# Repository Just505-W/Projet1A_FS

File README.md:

# Projet1A\_FS

Bienvenu sur le dépot GitHub d'un des groupes de Projet de première année de l'ENSEA.   
Participants du projet :   
BALLARD Athénaïs           NOICI Amélie  
EL GAAMOUCH Aïssa      VENTURA Arthur  
ELICE Bastien                    WOELFFEL Justine  
GERVAIS Joseph

Professeur encadrant : M.TAUVEL

## Dossiers utiles :

Projet Datalogger/SD d'un etudiant sur Git : https://github.com/crsz20/SDCard-Interface-STM32/tree/master

Régulateur de tension datasheet : https://www.alldatasheet.com/datasheet-pdf/view/807123/TI1/LM1117DT-3.3.html

Comment éditer un fichier GitHub : https://docs.github.com/fr/get-started/writing-on-github/getting-started-with-writing-and-formatting-on-github/basic-writing-and-formatting-syntax

Tutoriel de conception de PCB : https://jak-services.github.io/fr/tutorial\_kicad\_9\_build\_your\_first\_pcb.html

:warning: ***Remplir le fichier Suivi de projet.md à la fin de chaque séance !***

## Description du projet:

Ce projet a pour objectif de réaliser des composants utiles au bon fonctionnement d'une monoplace dans le cadre du concours **FORMULA STUDENT**. Un de ces composants est lui tiré du concours **PERSEUS**.

Le projet se concentre sur la conception et la fabrication de 3 PCB:

* Un capteur d'**Odométrie** : il calcule la vitesse de rotation des roues de la voitures et la transmet au bus CAN.
* Un capteur **BMS** (battery management system) : un système électronique permettant d’indiquer au conducteur la charge de la batterie en temps réel.

* Un **Datalogger**:  il récupère les données du bus CAN en temps réel et les stock dans un carte SD, qui servira de "boîte noire" en cas de destruction de l'appareil. Il sera également doté d'une application codée en Java (référence à notre super cours de **programmation orientée objet**) afin d'avoir une interface graphique utile à la conduite.

## Rôles

|Chef de projet|Odométrie|Datalogger|BMS|Software|
|:-:|:-:|:-:|:-:|:-:|
|Justine|Athénaïs|Aïssa \\ Joseph|Arthur|Amélie \\ Bastien|

## Odométrie Spécifications :

### Composants nécessaires + Datasheet :

* Microcontrôleur: STM32C092FCP6 (code : 4676916 - Farnell)
* Régulateur de tension : (code : 197-7195P - RS)
* Connecteur USB :
* 4 connecteurs d'entrée/sortie :
* 2 boutons poussoir : \~Interrupteur tactile traversant (code : 682-1254 - RS)\~
* 2 LED (LED de fonctionnement et de test) : (code : 466-3863 - RS)

## Datalogger Spécifications :

### Composants nécessaires + Datasheet :

* Microcontrôleur : STM32F042F6P6 (code : 2469549 - Farnell)
* 2 Régulateur de tension : Regulateur 3.3V (code : 197-7195P - RS) Régulateur 5.0V (code : 2534281 - Farnell)
* 4 connecteurs d'entrée/sortie :
* 1 Interrupteur : Interrupteur tactile traversant (code : 682-1254 - RS)
* 2 boutons poussoir :
* 2 LED (LED de fonctionnement et de test) : LED CMS  (code : 466-3863 - RS)

## Gestionnaire de Batterie (BMS) :

### Composants nécessaires + Datasheet :

* Microcontrôleur: STM32C092FCP6 (code : 4676916 - Farnell)
* Régulateur de tension : (code : 197-7195P - RS)
* 4 connecteurs d'entrée/sortie :
* 2 boutons poussoir : \~Interrupteur tactile traversant (code : 682-1254 - RS)\~
* 2 LED (LED de fonctionnement et de test) : (code : 466-3863 - RS)
* capteur à effet hall

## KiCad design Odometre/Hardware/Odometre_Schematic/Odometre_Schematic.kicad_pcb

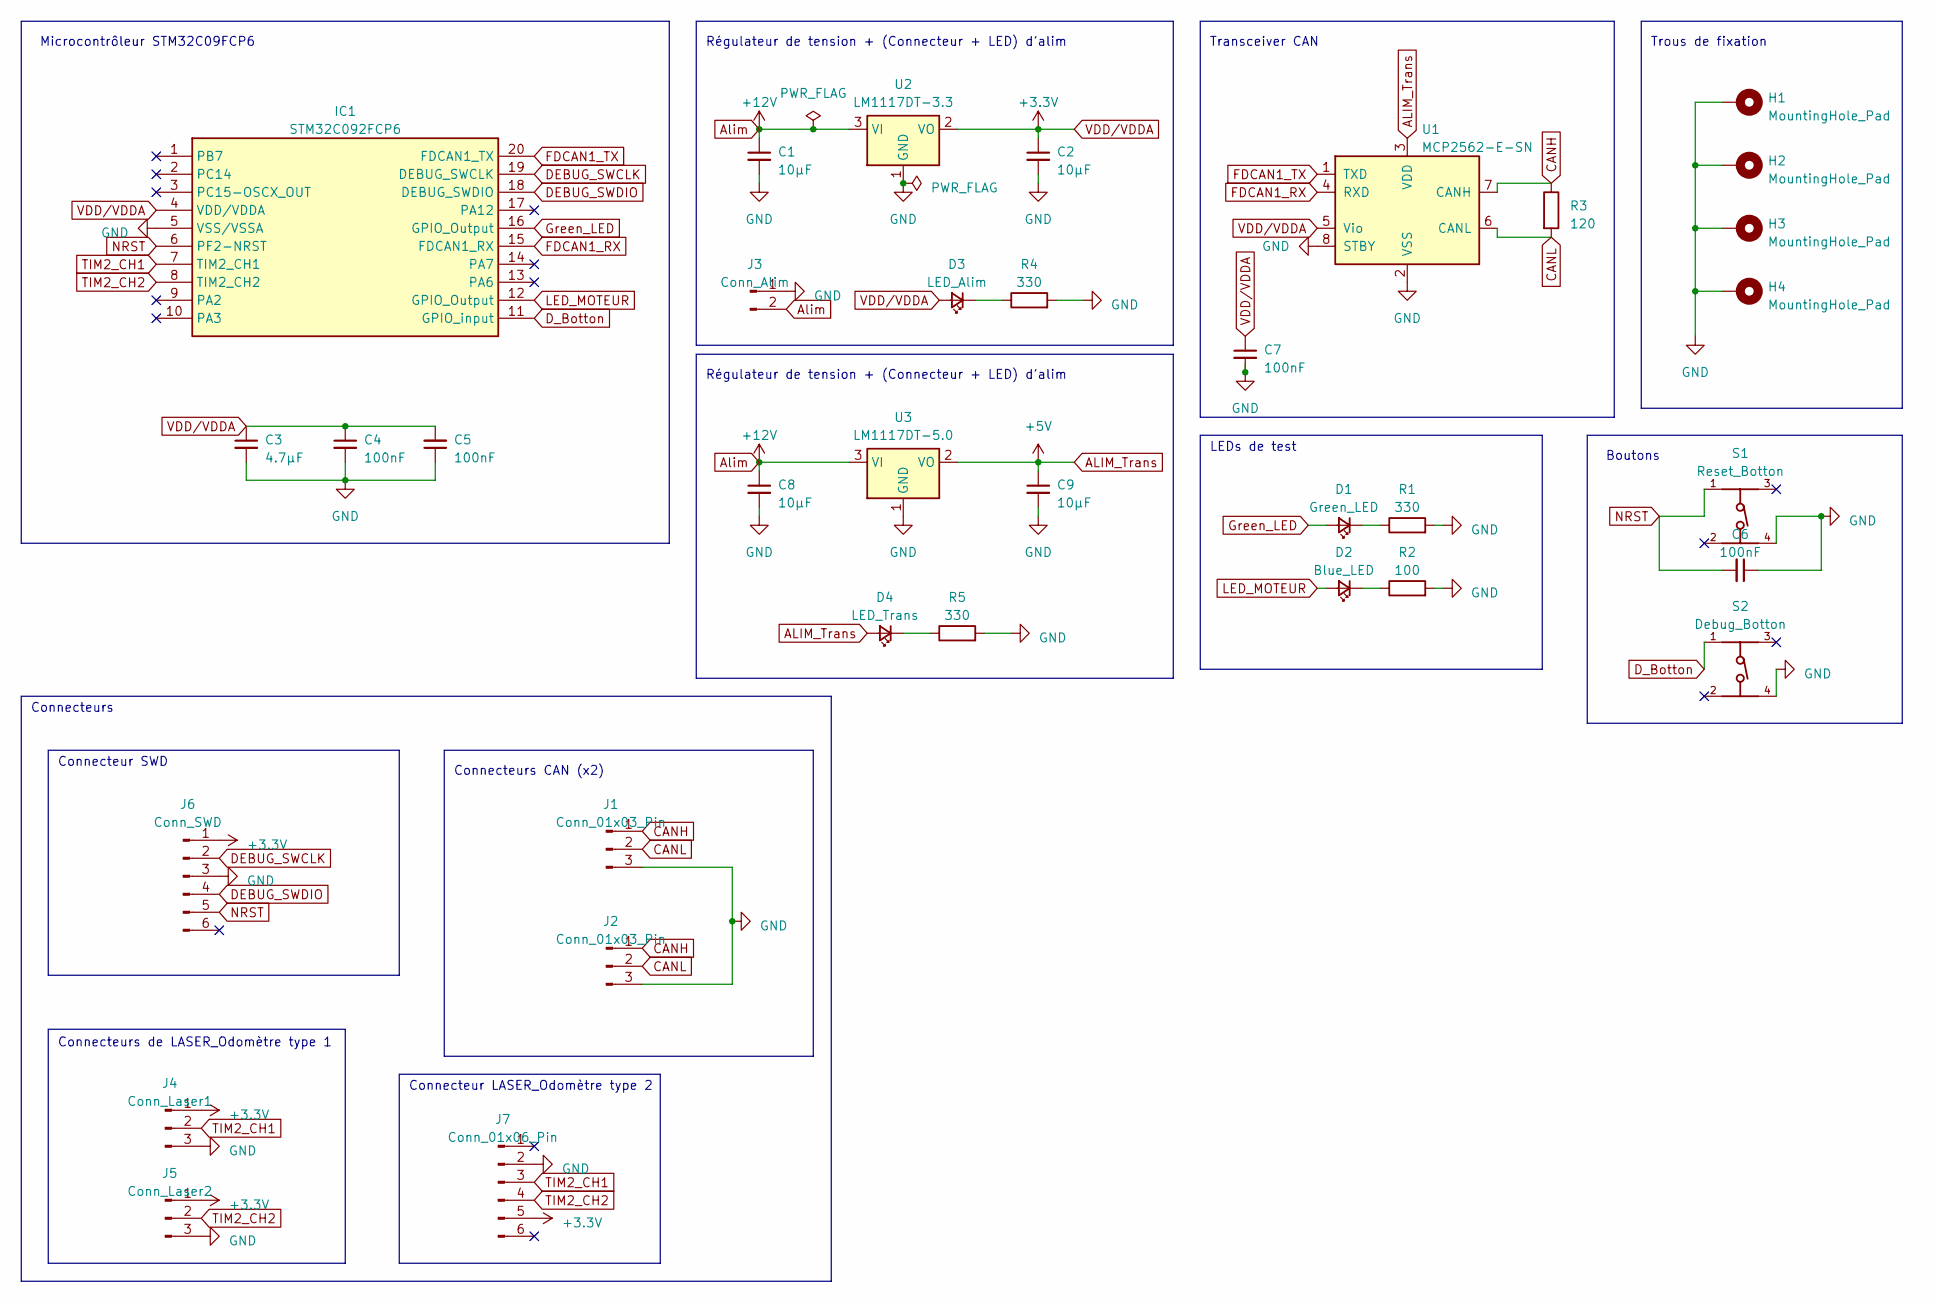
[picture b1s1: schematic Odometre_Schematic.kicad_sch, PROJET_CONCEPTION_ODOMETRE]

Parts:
C1, C2, C8, C9: 10µF; C_0805_2012Metric_Pad1.18x1.45mm_HandSolder
C3: 4.7µF; C_0805_2012Metric_Pad1.18x1.45mm_HandSolder
C4, C5, C6, C7: 100nF; C_0805_2012Metric_Pad1.18x1.45mm_HandSolder
D1: Green_LED; D_0603_1608Metric_Pad1.05x0.95mm_HandSolder
D2: Blue_LED; D_0603_1608Metric_Pad1.05x0.95mm_HandSolder
D3: LED_Alim; D_0603_1608Metric_Pad1.05x0.95mm_HandSolder
D4: LED_Trans; D_0603_1608Metric_Pad1.05x0.95mm_HandSolder
H1, H2, H3, H4: MountingHole_Pad; MountingHole_3.2mm_M3_DIN965_Pad
IC1: STM32C092FCP6; TSSOP-20_4.4x6.5mm_P0.65mm; Manufacturer_Part_Number STM32C092FCP6
J1, J2: Conn_01x03_Pin; JST_PH_B3B-PH-K_1x03_P2.00mm_Vertical
J3: Conn_Alim; JST_PH_B2B-PH-K_1x02_P2.00mm_Vertical
J4: Conn_Laser1; PinHeader_1x03_P2.54mm_Vertical
J5: Conn_Laser2; PinHeader_1x03_P2.54mm_Vertical
J6: Conn_SWD; PinHeader_1x06_P2.54mm_Vertical
J7: Conn_01x06_Pin; JST_PH_B6B-PH-K_1x06_P2.00mm_Vertical
R1, R4, R5: 330; R_0603_1608Metric_Pad0.98x0.95mm_HandSolder
R2: 100; R_0603_1608Metric_Pad0.98x0.95mm_HandSolder
R3: 120; R_0603_1608Metric_Pad0.98x0.95mm_HandSolder
S1: Reset_Botton; 430182043816
S2: Debug_Botton; 430182043816
U1: MCP2562-E-SN; SOIC-8_3.9x4.9mm_P1.27mm
U2: LM1117DT-3.3; TO-252-3_TabPin2
U3: LM1117DT-5.0; TO-252-3_TabPin2

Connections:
+3.3V: C2.1, C3.1, C4.1, C5.2, C7.1, D3.2 (A), IC1.4 (VDD/VDDA), J4.1, J5.1, J6.1, J7.5, U1.5 (Vio), U2.2 (VO)
+5V: C9.1, D4.2 (A), U1.3 (VDD), U3.2 (VO)
+12V: C1.1, C8.1, J3.2, U2.3 (VI), U3.3 (VI)
CANH: J1.1, J2.1, R3.1, U1.7 (CANH)
CANL: J1.2, J2.2, R3.2, U1.6 (CANL)
DEBUG_SWCLK: IC1.19 (PA14-BOOT0/PA15), J6.2
DEBUG_SWDIO: IC1.18 (PA13), J6.4
D_Botton: IC1.11 (PA4), S2.1
FDCAN1_RX: IC1.15 (PB0/PB1/PB2/PA8), U1.4 (RXD)
FDCAN1_TX: IC1.20 (PB3/PB4/PB5/PB6), U1.1 (TXD)
GND: C1.2, C2.2, C3.2, C4.2, C5.1, C6.1, C7.2, C8.2, C9.2, H1.1, H2.1, H3.1, H4.1, IC1.5 (VSS/VSSA), J1.3, J2.3, J3.1, J4.3, J5.3, J6.3, J7.2, R1.2, R2.2, R4.2, R5.2, S1.4, S2.4, U1.2 (VSS), U1.8 (STBY), U2.1 (GND), U3.1 (GND)
Green_LED: D1.2 (A), IC1.16 (PA11_[PA9])
LED_MOTEUR: D2.2 (A), IC1.12 (PA5)
NRST: C6.2, IC1.6 (PF2-NRST), J6.5, S1.1
unnamed: D1.1 (K), R1.1
unnamed: D2.1 (K), R2.1
unnamed: D3.1 (K), R4.1
unnamed: D4.1 (K), R5.1
TIM2_CH1: IC1.7 (PA0), J4.2, J7.3
TIM2_CH2: IC1.8 (PA1), J5.2, J7.4

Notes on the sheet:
LEDs de test
Transceiver CAN
Connecteurs CAN (x2)
Régulateur de tension + (Connecteur + LED) d'alim
Connecteur SWD
Connecteurs de LASER_Odomètre type 1
Connecteurs
Boutons
Connecteur LASER_Odomètre type 2
Microcontrôleur STM32C09FCP6
Trous de fixation

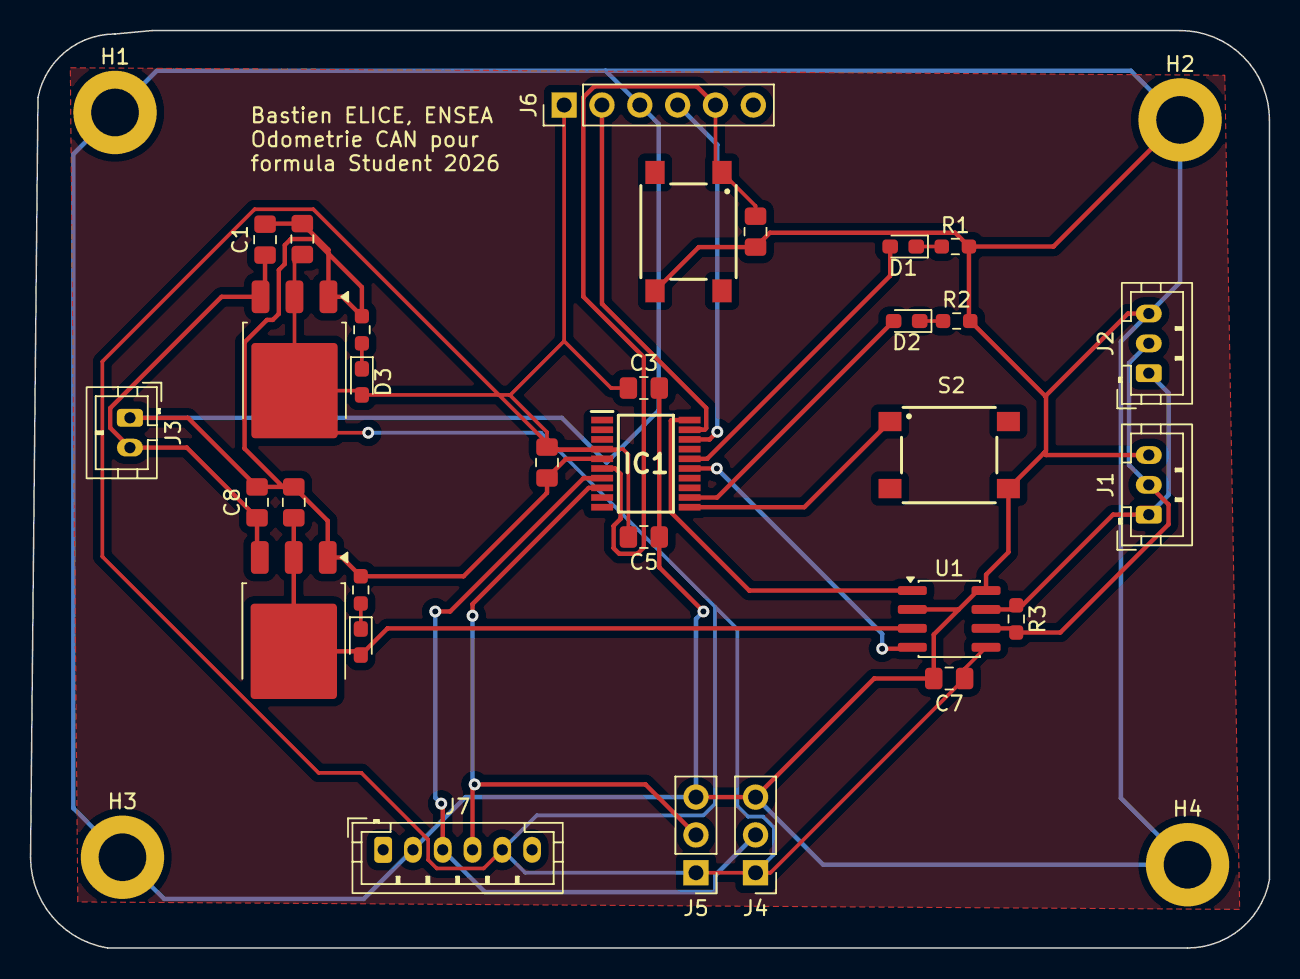
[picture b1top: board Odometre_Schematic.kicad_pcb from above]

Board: 2 copper layers, 83.2 x 61.6 mm, 35 parts (0 on the bottom side), 20 nets.

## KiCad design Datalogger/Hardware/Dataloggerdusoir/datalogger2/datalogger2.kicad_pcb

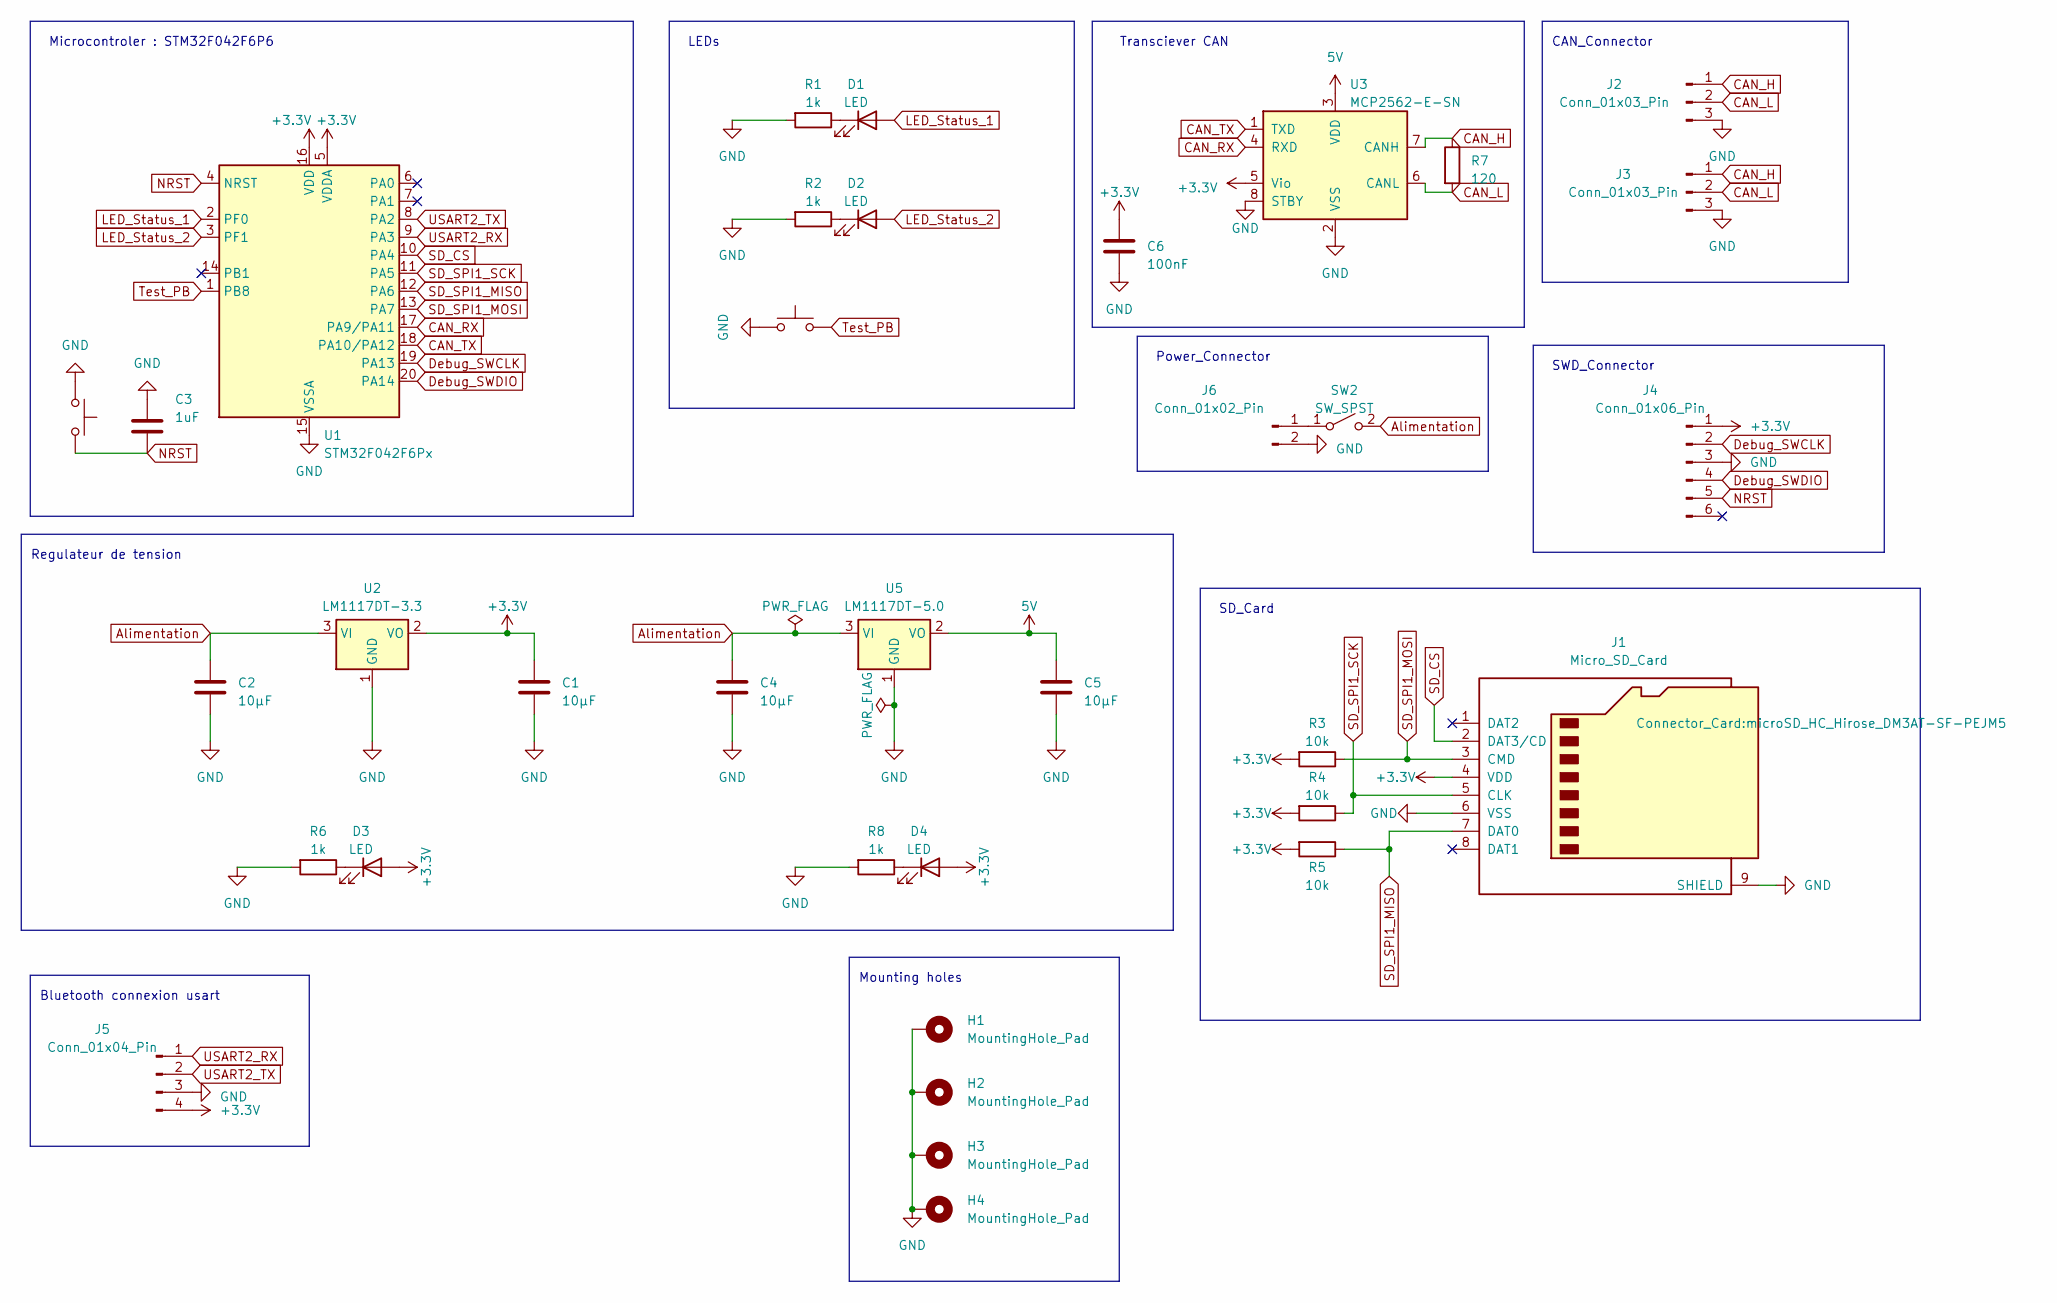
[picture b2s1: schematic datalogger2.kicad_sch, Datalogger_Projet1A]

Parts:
C1, C2, C4, C5: 10µF; C_0603_1608Metric_Pad1.08x0.95mm_HandSolder
C3: 1uF; C_0603_1608Metric_Pad1.08x0.95mm_HandSolder
C6: 100nF; C_0603_1608Metric_Pad1.08x0.95mm_HandSolder
D1, D2, D3, D4: LED; D_0603_1608Metric_Pad1.05x0.95mm_HandSolder
H1, H2, H3, H4: MountingHole_Pad; MountingHole_3.2mm_M3_DIN965_Pad
J1: Micro_SD_Card; microSD_HC_Hirose_DM3AT-SF-PEJM5
J2, J3: Conn_01x03_Pin; FanPinHeader_1x03_P2.54mm_Vertical
J4: Conn_01x06_Pin; PinHeader_1x06_P2.54mm_Vertical
J5: Conn_01x04_Pin; FanPinHeader_1x04_P2.54mm_Vertical
J6: Conn_01x02_Pin; JST_XH_B2B-XH-A_1x02_P2.50mm_Vertical
R1, R2, R6, R8: 1k; R_0603_1608Metric_Pad0.98x0.95mm_HandSolder
R3, R4, R5: 10k; R_0603_1608Metric_Pad0.98x0.95mm_HandSolder
R7: 120; R_0603_1608Metric_Pad0.98x0.95mm_HandSolder
SW1, SW3: SW_Push; SW_PUSH_6mm
SW2: SW_SPST; SW_PUSH_6mm
U1: STM32F042F6Px; TSSOP-20_4.4x6.5mm_P0.65mm
U2: LM1117DT-3.3; TO-252-3_TabPin2
U3: MCP2562-E-SN; SOIC-8_3.9x4.9mm_P1.27mm
U5: LM1117DT-5.0; TO-252-3_TabPin2

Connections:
Alimentation: C2.1, C4.1, SW2.2 (B), U2.3 (VI), U5.3 (VI)
CAN_H: J2.1, J3.1, R7.1, U3.7 (CANH)
CAN_L: J2.2, J3.2, R7.2, U3.6 (CANL)
CAN_RX: U1.17 (PA9/PA11), U3.4 (RXD)
CAN_TX: U1.18 (PA10/PA12), U3.1 (TXD)
Debug_SWCLK: J4.2, U1.19 (PA13)
Debug_SWDIO: J4.4, U1.20 (PA14)
GND: C1.2, C2.2, C3.1, C4.2, C5.2, C6.2, H1.1, H2.1, H3.1, H4.1, J1.6 (VSS), J1.9 (SHIELD), J2.3, J3.3, J4.3, J5.3, J6.2, R1.2, R2.2, R6.2, R8.2, SW1.1, SW3.1, U1.15 (VSSA), U2.1 (GND), U3.2 (VSS), U3.8 (STBY), U5.1 (GND); also elsewhere on the board
LED_Status_1: D1.2 (A), U1.2 (PF0)
LED_Status_2: D2.2 (A), U1.3 (PF1)
NRST: C3.2, J4.5, SW1.2, U1.4 (NRST)
unnamed: D1.1 (K), R1.1
unnamed: D2.1 (K), R2.1
unnamed: D3.1 (K), R6.1
unnamed: D4.1 (K), R8.1
unnamed: J6.1, SW2.1 (A)
SD_CS: J1.2 (DAT3/CD), U1.10 (PA4)
SD_SPI1_MISO: J1.7 (DAT0), R5.1, U1.12 (PA6)
SD_SPI1_MOSI: J1.3 (CMD), R3.1, U1.13 (PA7)
SD_SPI1_SCK: J1.5 (CLK), R4.1, U1.11 (PA5)
Test_PB: SW3.2, U1.1 (PB8)
USART2_RX: J5.1, U1.9 (PA3)
USART2_TX: J5.2, U1.8 (PA2)

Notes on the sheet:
Mounting holes
CAN_Connector
SD_Card
Power_Connector
Transciever CAN
LEDs
Regulateur de tension
Bluetooth connexion usart
SWD_Connector
Microcontroler : STM32F042F6P6

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
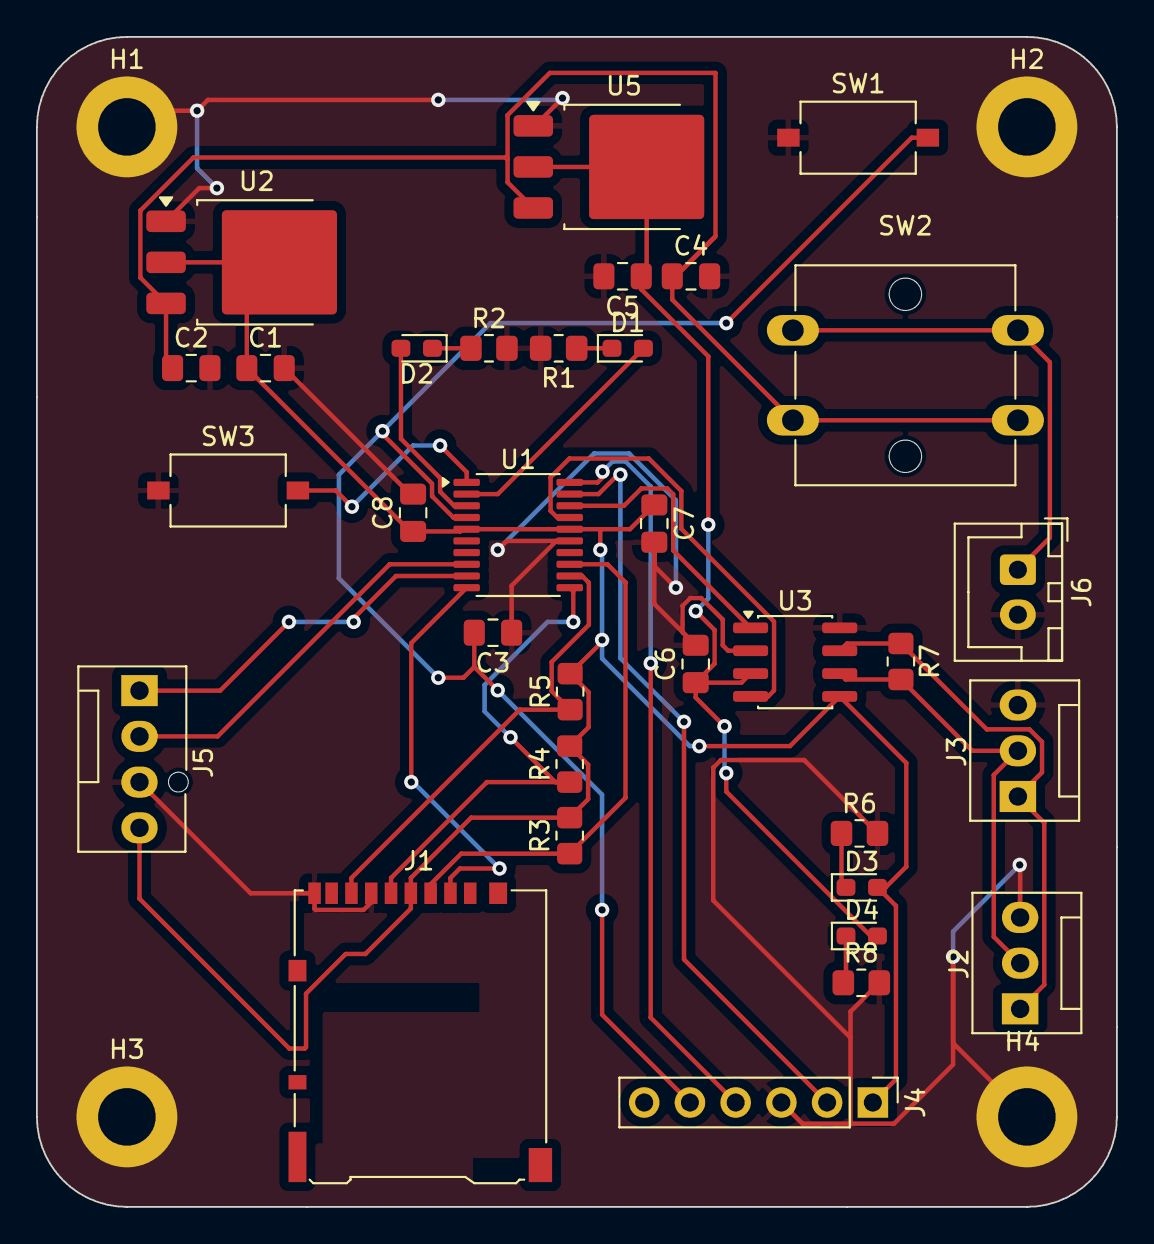
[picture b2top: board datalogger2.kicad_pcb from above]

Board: 2 copper layers, 60.0 x 65.0 mm, 37 parts (0 on the bottom side), 25 nets.

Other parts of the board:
C7, C8: 100nF; C_0805_2012Metric_Pad1.18x1.45mm_HandSolder

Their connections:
GND: C7.2, C8.2; also elsewhere on the board

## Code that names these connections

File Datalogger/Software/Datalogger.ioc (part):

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Mcu.Name=STM32F042F6Px
Mcu.Package=TSSOP20
Mcu.UserName=STM32F042F6Px
PA0.GPIOParameters=GPIO_PuPd,GPIO_Label
PA0.GPIO_Label=Test_PB
PA0.GPIO_PuPd=GPIO_PULLUP
PA0.Signal=GPIO_Input
PA11.Mode=CAN_Activate
PA11.Signal=CAN_RX
PA12.Mode=CAN_Activate
PA12.Signal=CAN_TX
PA13.GPIOParameters=GPIO_Label
PA13.GPIO_Label=Debug_SWDIO
PA13.Mode=Serial_Wire
PA13.Signal=SYS_SWDIO
PA14.GPIOParameters=GPIO_Label
PA14.GPIO_Label=Debug_SWCLK
PA14.Mode=Serial_Wire
PA14.Signal=SYS_SWCLK
PA2.Mode=Asynchronous
PA2.Signal=USART2_TX
PA3.Mode=Asynchronous
PA3.Signal=USART2_RX
PA4.GPIOParameters=GPIO_Label
PA4.GPIO_Label=SD_CS
PA4.Signal=GPIO_Output
PA5.GPIOParameters=GPIO_Label
PA5.GPIO_Label=SD_SPI1_SCK
PA5.Mode=Full_Duplex_Master
PA5.Signal=SPI1_SCK
PA6.GPIOParameters=GPIO_Label
PA6.GPIO_Label=SD_SPI1_MISO
PA6.Mode=Full_Duplex_Master
PA6.Signal=SPI1_MISO
PA7.GPIOParameters=GPIO_Label
PA7.GPIO_Label=SD_SPI1_MOSI
PA7.Mode=Full_Duplex_Master
PA7.Signal=SPI1_MOSI
PF0-OSC_IN.GPIOParameters=GPIO_Label
PF0-OSC_IN.GPIO_Label=LED_Status_1
PF0-OSC_IN.Signal=GPIO_Output
PF1-OSC_OUT.GPIOParameters=GPIO_Label
PF1-OSC_OUT.GPIO_Label=LED_Status_2
PF1-OSC_OUT.Signal=GPIO_Output
board=custom

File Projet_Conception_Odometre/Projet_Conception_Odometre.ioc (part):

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Mcu.Name=STM32C092FCPx
Mcu.Package=TSSOP20
Mcu.UserName=STM32C092FCPx
PA0.Signal=S_TIM2_CH1
PA1.Signal=S_TIM2_CH2
PA11\ [PA9].Signal=GPIO_Output
PA12\ [PA10].Signal=GPIO_Input
PA13.Mode=Serial_Wire
PA13.Signal=DEBUG_SWDIO
PA14-BOOT0.Mode=Serial_Wire
PA14-BOOT0.Signal=DEBUG_SWCLK
PA14-BOOT0__PA15.StandardMode=true
PA2.Signal=USART2_TX
PA3.Signal=USART2_RX
PA5.Signal=GPIO_Output
PB0.Mode=FDCAN_Activate
PB0.Signal=FDCAN1_RX
PB0__PB1__PB2__PA8.StandardMode=true
PB3__PB4__PB5__PB6.StandardMode=true
PB6.Mode=FDCAN_Activate
PB6.Signal=FDCAN1_TX
PB7__PB8.StandardMode=true
RCC.HSE_VALUE=8000000
RCC.SYSCLKFreq_VALUE=12000000
board=custom

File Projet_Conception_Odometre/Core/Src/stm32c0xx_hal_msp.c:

/* USER CODE BEGIN Header */
/**
  ******************************************************************************
  * @file         stm32c0xx_hal_msp.c
  * @brief        This file provides code for the MSP Initialization
  *               and de-Initialization codes.
  ******************************************************************************
  * @attention
  *
  * Copyright (c) 2026 STMicroelectronics.
  * All rights reserved.
  *
  * This software is licensed under terms that can be found in the LICENSE file
  * in the root directory of this software component.
  * If no LICENSE file comes with this software, it is provided AS-IS.
  *
  ******************************************************************************
  */
/* USER CODE END Header */

/* Includes ------------------------------------------------------------------*/
#include "main.h"
/* USER CODE BEGIN Includes */

/* USER CODE END Includes */

/* Private typedef -----------------------------------------------------------*/
/* USER CODE BEGIN TD */

/* USER CODE END TD */

/* Private define ------------------------------------------------------------*/
/* USER CODE BEGIN Define */

/* USER CODE END Define */

/* Private macro -------------------------------------------------------------*/
/* USER CODE BEGIN Macro */

/* USER CODE END Macro */

/* Private variables ---------------------------------------------------------*/
/* USER CODE BEGIN PV */

/* USER CODE END PV */

/* Private function prototypes -----------------------------------------------*/
/* USER CODE BEGIN PFP */

/* USER CODE END PFP */

/* External functions --------------------------------------------------------*/
/* USER CODE BEGIN ExternalFunctions */

/* USER CODE END ExternalFunctions */

/* USER CODE BEGIN 0 */

/* USER CODE END 0 */
/**
  * Initializes the Global MSP.
  */
void HAL_MspInit(void)
{

  /* USER CODE BEGIN MspInit 0 */

  /* USER CODE END MspInit 0 */

  __HAL_RCC_SYSCFG_CLK_ENABLE();
  __HAL_RCC_PWR_CLK_ENABLE();

  /* System interrupt init*/

  /* USER CODE BEGIN MspInit 1 */

  /* USER CODE END MspInit 1 */
}

/**
  * @brief FDCAN MSP Initialization
  * This function configures the hardware resources used in this example
  * @param hfdcan: FDCAN handle pointer
  * @retval None
  */
void HAL_FDCAN_MspInit(FDCAN_HandleTypeDef* hfdcan)
{
  GPIO_InitTypeDef GPIO_InitStruct = {0};
  RCC_PeriphCLKInitTypeDef PeriphClkInit = {0};
  if(hfdcan->Instance==FDCAN1)
  {
    /* USER CODE BEGIN FDCAN1_MspInit 0 */

    /* USER CODE END FDCAN1_MspInit 0 */

  /** Initializes the peripherals clocks
  */
    PeriphClkInit.PeriphClockSelection = RCC_PERIPHCLK_FDCAN1;
    PeriphClkInit.Fdcan1ClockSelection = RCC_FDCAN1CLKSOURCE_PCLK1;
    if (HAL_RCCEx_PeriphCLKConfig(&PeriphClkInit) != HAL_OK)
    {
      Error_Handler();
    }

    /* Peripheral clock enable */
    __HAL_RCC_FDCAN1_CLK_ENABLE();

    __HAL_RCC_GPIOB_CLK_ENABLE();
    /**FDCAN1 GPIO Configuration
    PB0     ------> FDCAN1_RX
    PB6     ------> FDCAN1_TX
    */
    GPIO_InitStruct.Pin = GPIO_PIN_0;
    GPIO_InitStruct.Mode = GPIO_MODE_AF_PP;
    GPIO_InitStruct.Pull = GPIO_NOPULL;
    GPIO_InitStruct.Speed = GPIO_SPEED_FREQ_LOW;
    GPIO_InitStruct.Alternate = GPIO_AF3_FDCAN1;
    HAL_GPIO_Init(GPIOB, &GPIO_InitStruct);

    GPIO_InitStruct.Pin = GPIO_PIN_6;
    GPIO_InitStruct.Mode = GPIO_MODE_AF_PP;
    GPIO_InitStruct.Pull = GPIO_NOPULL;
    GPIO_InitStruct.Speed = GPIO_SPEED_FREQ_LOW;
    GPIO_InitStruct.Alternate = GPIO_AF15_EVENTOUT;
    HAL_GPIO_Init(GPIOB, &GPIO_InitStruct);

    /* USER CODE BEGIN FDCAN1_MspInit 1 */

    /* USER CODE END FDCAN1_MspInit 1 */

  }

}

/**
  * @brief FDCAN MSP De-Initialization
  * This function freeze the hardware resources used in this example
  * @param hfdcan: FDCAN handle pointer
  * @retval None
  */
void HAL_FDCAN_MspDeInit(FDCAN_HandleTypeDef* hfdcan)
{
  if(hfdcan->Instance==FDCAN1)
  {
    /* USER CODE BEGIN FDCAN1_MspDeInit 0 */

    /* USER CODE END FDCAN1_MspDeInit 0 */
    /* Peripheral clock disable */
    __HAL_RCC_FDCAN1_CLK_DISABLE();

    /**FDCAN1 GPIO Configuration
    PB0     ------> FDCAN1_RX
    PB6     ------> FDCAN1_TX
    */
    HAL_GPIO_DeInit(GPIOB, GPIO_PIN_0|GPIO_PIN_6);

    /* USER CODE BEGIN FDCAN1_MspDeInit 1 */

    /* USER CODE END FDCAN1_MspDeInit 1 */
  }

}

/**
  * @brief TIM_Encoder MSP Initialization
  * This function configures the hardware resources used in this example
  * @param htim_encoder: TIM_Encoder handle pointer
  * @retval None
  */
void HAL_TIM_Encoder_MspInit(TIM_HandleTypeDef* htim_encoder)
{
  GPIO_InitTypeDef GPIO_InitStruct = {0};
  if(htim_encoder->Instance==TIM2)
  {
    /* USER CODE BEGIN TIM2_MspInit 0 */

    /* USER CODE END TIM2_MspInit 0 */
    /* Peripheral clock enable */
    __HAL_RCC_TIM2_CLK_ENABLE();

    __HAL_RCC_GPIOA_CLK_ENABLE();
    /**TIM2 GPIO Configuration
    PA0     ------> TIM2_CH1
    PA1     ------> TIM2_CH2
    */
    GPIO_InitStruct.Pin = GPIO_PIN_0|GPIO_PIN_1;
    GPIO_InitStruct.Mode = GPIO_MODE_AF_PP;
    GPIO_InitStruct.Pull = GPIO_NOPULL;
    GPIO_InitStruct.Speed = GPIO_SPEED_FREQ_LOW;
    GPIO_InitStruct.Alternate = GPIO_AF3_TIM2;
    HAL_GPIO_Init(GPIOA, &GPIO_InitStruct);

    /* TIM2 interrupt Init */
    HAL_NVIC_SetPriority(TIM2_IRQn, 0, 0);
    HAL_NVIC_EnableIRQ(TIM2_IRQn);
    /* USER CODE BEGIN TIM2_MspInit 1 */

    /* USER CODE END TIM2_MspInit 1 */

  }

}

/**
  * @brief TIM_Encoder MSP De-Initialization
  * This function freeze the hardware resources used in this example
  * @param htim_encoder: TIM_Encoder handle pointer
  * @retval None
  */
void HAL_TIM_Encoder_MspDeInit(TIM_HandleTypeDef* htim_encoder)
{
  if(htim_encoder->Instance==TIM2)
  {
    /* USER CODE BEGIN TIM2_MspDeInit 0 */

    /* USER CODE END TIM2_MspDeInit 0 */
    /* Peripheral clock disable */
    __HAL_RCC_TIM2_CLK_DISABLE();

    /**TIM2 GPIO Configuration
    PA0     ------> TIM2_CH1
    PA1     ------> TIM2_CH2
    */
    HAL_GPIO_DeInit(GPIOA, GPIO_PIN_0|GPIO_PIN_1);

    /* TIM2 interrupt DeInit */
    HAL_NVIC_DisableIRQ(TIM2_IRQn);
    /* USER CODE BEGIN TIM2_MspDeInit 1 */

    /* USER CODE END TIM2_MspDeInit 1 */
  }

}

/* USER CODE BEGIN 1 */

/* USER CODE END 1 */

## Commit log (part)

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2026-02-09 Nettoyage: suppression de metadata et logs
2026-02-09 ajout de fonctions dans les fichiers
2026-02-09 grand nettoyage
2026-02-09 création d'un fichier .ioc
2026-02-09 création de fichiers utiles
2026-02-09 modif du .gitignore
2026-02-09 ajout de fichiers
2026-02-09 ajout du fichier .ioc
2026-02-09 ajout de fichier de code
2026-02-10 création du KiCad
2026-02-10 schematic kicad
2026-02-11 auto-save kicad
2026-02-11 autosave kicad
2026-02-11 modification
    suppression d'un pin gpio input
2026-02-11 modif
2026-02-11 modifs
2026-02-11 Datalogger
2026-02-11 DAtalog+réorganisation dossiers
2026-02-11 modif kicad
2026-02-11 c'est réglé
2026-02-11 Datalog_sch
2026-02-11 modif du fichier ioc et du fiichier kicad
2026-02-12 changement de connecteur
2026-02-12 Changement d'assocation
2026-02-12 modif tension d'entrée
2026-02-12 Echange µF et C
2026-02-12 modif hardware
2026-02-12 Modif affectation
2026-02-12 réorganisation du schematic
2026-02-12 Kikad Sch ok
2026-02-12 Interrupetur .ioc modif
2026-02-12 modif dossier
2026-02-12 modif kicad indications
2026-02-12 odo modif
2026-02-12 modification d'une pin dans l'ioc
2026-02-12 read me datalogger
2026-02-12 modif ioc
2026-02-12 modif shematic
2026-02-12 ajout de datasheets
2026-02-12 Datasheet regulateur
2026-02-12 Kikad final
2026-02-12 .ioc final datalogger
2026-02-12 Schéma kicad avec empreinte
2026-02-12 suivit de projet
2026-02-12 re datalog
2026-02-12 ajout d'empreintes
2026-02-12 bons de commande
2026-02-12 modif de l'arborescence
2026-02-13 Oublie
2026-02-16 DATALOGGER avec empreinte
2026-02-17 rien de spécial
2026-02-17 fin schématic
2026-02-18 update schématic
2026-02-18 routage début
2026-02-19 never mind
2026-02-19 modif de la valeur de sortie de regulateur
2026-02-19 shematic+pcb
2026-02-19 schematic odomètre définitif
2026-02-19 Datalogger 19/02/2026 8h
2026-02-19 datalogger 0906
2026-02-19 schematic vf
2026-02-19 readme
2026-02-19 import d'empreinte
2026-02-19 footprint modifiées
2026-02-19 import empreintes
2026-02-19 schematic et pcb
2026-02-19 import empreinte
2026-02-19 modif empreintes
2026-02-19 modifs che pas
2026-02-19 Datalogger 19/02/2026 13:33
2026-02-19 routage du pcb
2026-02-19 Datalogger Final
2026-02-19 modif d'empreintes
2026-02-19 mise à jour PCB
2026-02-20 rien de nouveau
2026-02-23 rangement hardware/software test datalog
2026-02-23 suivit image datalog
2026-02-23 rere
2026-03-12 Modification PCB pour impression
2026-03-19 MircoSD commande
2026-03-26 création de code
2026-03-26 Push
2026-03-26 avancé dans le code
2026-03-26 no sé
2026-03-26 chill
2026-03-26 suppression d'un fichier inutile
2026-03-26 suppression d'un commentaire
2026-04-09 dataloggcubeide
2026-04-09 code datalog+help code
2026-04-09 BMS schematic
2026-04-16 Rangement Datalogger
    un peu d'ordre pr pas se perdre avec tt les version qu'il y avait
2026-04-16 rangement bis
2026-04-16 change
2026-04-16 pcb du gestionnaire de batterie
2026-04-16 Création des fichiers de fabrication
2026-05-07 zert
2026-05-21 look
2026-05-21 Rangement definitif github
2026-05-21 datalogger code
2026-05-21 mise à jour git (Odo & BMS)
2026-05-21 Renommer dossier
2026-05-21 Renommer
2026-05-21 Revert "Merge branch 'main' of https://github.com/Just505-W/Projet1A_FS"
    This reverts commit c1e37d3423cafb9423d1164653e3db663409ee41, reversing
    changes made to a15b194debe0785e58251c42356ed53677aeb81e.
2026-05-22 datalog code
2026-05-23 Images
2026-05-23 datalogger code sd
2026-05-24 rapport
2026-05-24 changement de commentaire
